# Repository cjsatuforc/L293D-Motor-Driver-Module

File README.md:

# L293D-Motor-Driver-Module
A dual motor driver module compatible with Arduino, Raspberry Pi, ESP family, etc

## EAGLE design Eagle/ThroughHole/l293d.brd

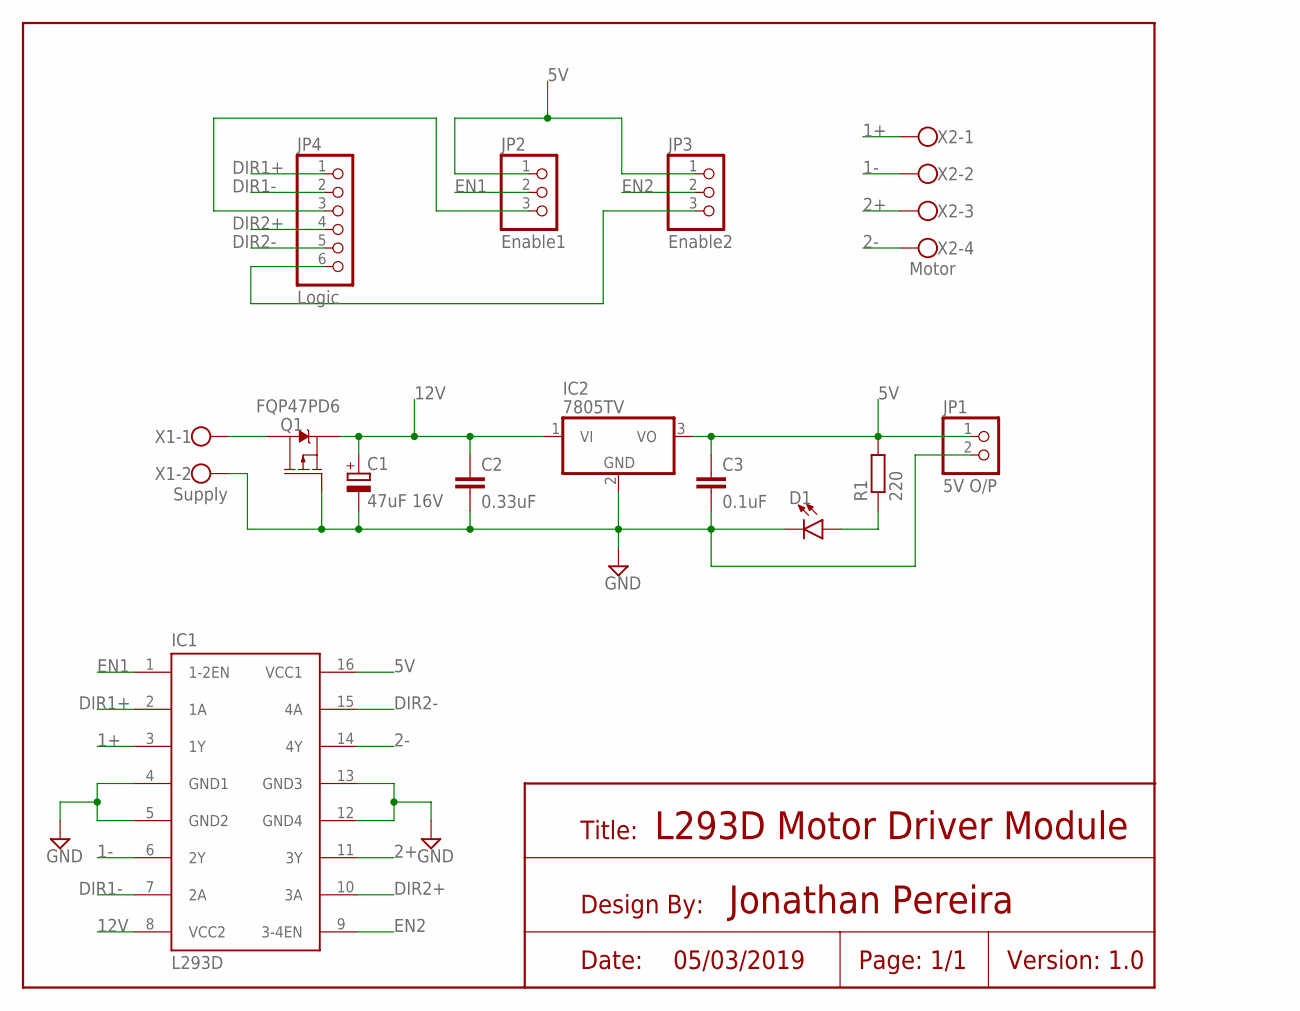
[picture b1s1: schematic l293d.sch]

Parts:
C1: 47uF 16V; E2,5-5
C2: 0.33uF; C025-024X044
C3: 0.1uF; C025-024X044
D1: LED5MM; LED_5MM
IC1: L293D; DIL16
IC2: 7805TV; TO220V
JP1: 5V O/P; 1X02
JP2: Enable1; 1X03
JP3: Enable2; 1X03
JP4: Logic; 1X06
Q1: FQP47PD6; TO220V
R1: 220; 0204/5
X1: Supply; W237-102
X2: Motor; W237-4

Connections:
1+: IC1.3 (1Y), X2.1
1-: IC1.6 (2Y), X2.2
2+: IC1.11 (3Y), X2.3
2-: IC1.14 (4Y), X2.4
5V: C3.1, IC1.16 (VCC1), IC2.3 (VO), JP1.1, JP2.1, JP3.1, R1.2
12V: C1.+, C2.1, IC1.8 (VCC2), IC2.1 (VI), Q1.3 (S)
DIR1+: IC1.2 (1A), JP4.1
DIR1-: IC1.7 (2A), JP4.2
DIR2+: IC1.10 (3A), JP4.4
DIR2-: IC1.15 (4A), JP4.5
EN1: IC1.1 (1-2EN), JP2.2
EN2: IC1.9 (3-4EN), JP3.2
GND: C1.-, C2.2, C3.2, D1.K (C), IC1.4 (GND1), IC1.5 (GND2), IC1.12 (GND4), IC1.13 (GND3), IC2.2 (GND), JP1.2, Q1.1 (G), X1.2
unnamed: D1.A, R1.1
unnamed: Q1.2 (D), X1.1
unnamed: JP2.3, JP4.3
unnamed: JP3.3, JP4.6

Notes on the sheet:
L293D Motor Driver Module
Title:
Design By:
Date:
Page: 1/1
Jonathan Pereira
05/03/2019
Version: 1.0

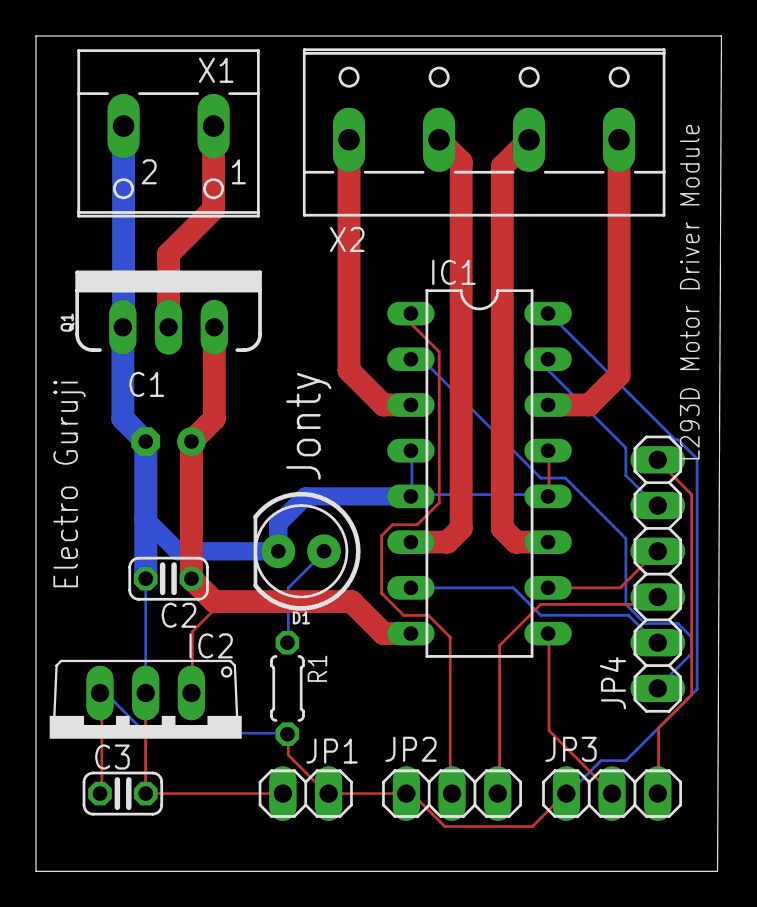
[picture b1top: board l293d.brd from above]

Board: 2 copper layers, 38.1 x 46.4 mm, 14 parts (1 on the bottom side), 17 nets.

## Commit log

2019-02-18 KiCAD files
    Board + Schematic
    Img
2019-03-06 Eagle
2019-03-06 Eagle Bottom Only
    For Homemade PCB on single side PCB.
2019-03-06 Update issue templates
    Bug report
2019-03-06 Update issue templates
2019-03-06 Eagle: Printable
2019-03-06 Language

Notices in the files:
parts and their libraries:
SparkFun-LED: Licensing: Creative Commons ShareAlike 4.0 International - https://creativecommons.org/licenses/by-sa/4.0
